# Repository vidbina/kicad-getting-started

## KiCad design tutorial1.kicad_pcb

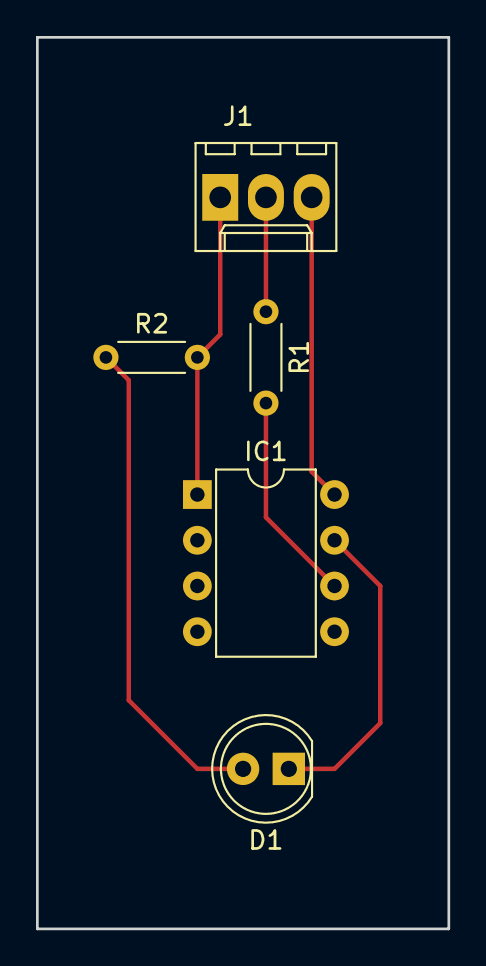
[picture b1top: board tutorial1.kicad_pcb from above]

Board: 2 copper layers, 22.9 x 49.5 mm, 5 parts (0 on the bottom side), 6 nets.

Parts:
D1: LED; LED_D5.0mm
IC1: PIC12C508A-I/SN; DIP-8_W7.62mm
J1: MYCONN3; Molex_KK-6410-03_03x2.54mm_Straight
R1: 100; R_Axial_DIN0204_L3.6mm_D1.6mm_P5.08mm_Horizontal
R2: 1k; R_Axial_DIN0204_L3.6mm_D1.6mm_P5.08mm_Horizontal

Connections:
/INPUT: IC1.6, R1.2
/INPUTtoR: J1.2, R1.1
/uCtoLED: D1.1, IC1.7
GND: IC1.8, J1.3
unnamed: D1.2, R2.1
VCC: IC1.1, J1.1, R2.2

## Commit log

2017-08-10 late to the party :bolt:
2017-09-05 busses
2017-09-05 bus labels
2017-09-09 more busses
2017-09-09 .xml
2017-09-10 changed J1 footprint to Molex
